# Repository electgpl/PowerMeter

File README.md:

# Power Meter v1 

Este es un medidor de potencia continua y alterna diseñado en base al microcontrolador AVR linea MEGA compatible ArduinoIDE.

  - Core AVR - **ARDUINO PRO MINI 5V**
  - Bootloader UART Arduino Compatible
  - ISP Compatible
  - Serial Terminal/Debug
  - Puerto para LCD I2C
  - Medidor de corriente ACS712 (Compatible 5, 20 y 30A) 
  - Medidor de Tensión **Directo** con atenuación resistiva y montado sobre 2.5V (Cero)
  - Fuente de alimentación integrada

## Lenguajes Compatibles

  - C
  - C++
  - Basic
  - Ensamblador
  - Ladder
  - y mas...
  
## Diseño y Desarrollo

> Diseñado en dos capas con SMD y THT
> Los componentes SMD son extraídos directamente de una placa Arduino Pro Mini 5V y Modulo ACS712
> Los componentes THT se adquieren con facilidad en los comercios.
>                           
> PCB creado en [JLCPCB].
> Diseño realizado en [Eagle].

### Instalación

Todos los archivos se encuentran disponibles en este repositorio, diagramas, pcb, etc...

### Pendientes

 - Código para el medidor de continua para la incorporación en fuentes de alimentación.
 - Mejoras en la aislación de seguridad eléctrica

License
----

MIT

**Free Software, Hell Yeah!**

[JLCPCB]: <https://jlcpcb.com/>
[Eagle]: <https://www.autodesk.com/products/eagle/overview>

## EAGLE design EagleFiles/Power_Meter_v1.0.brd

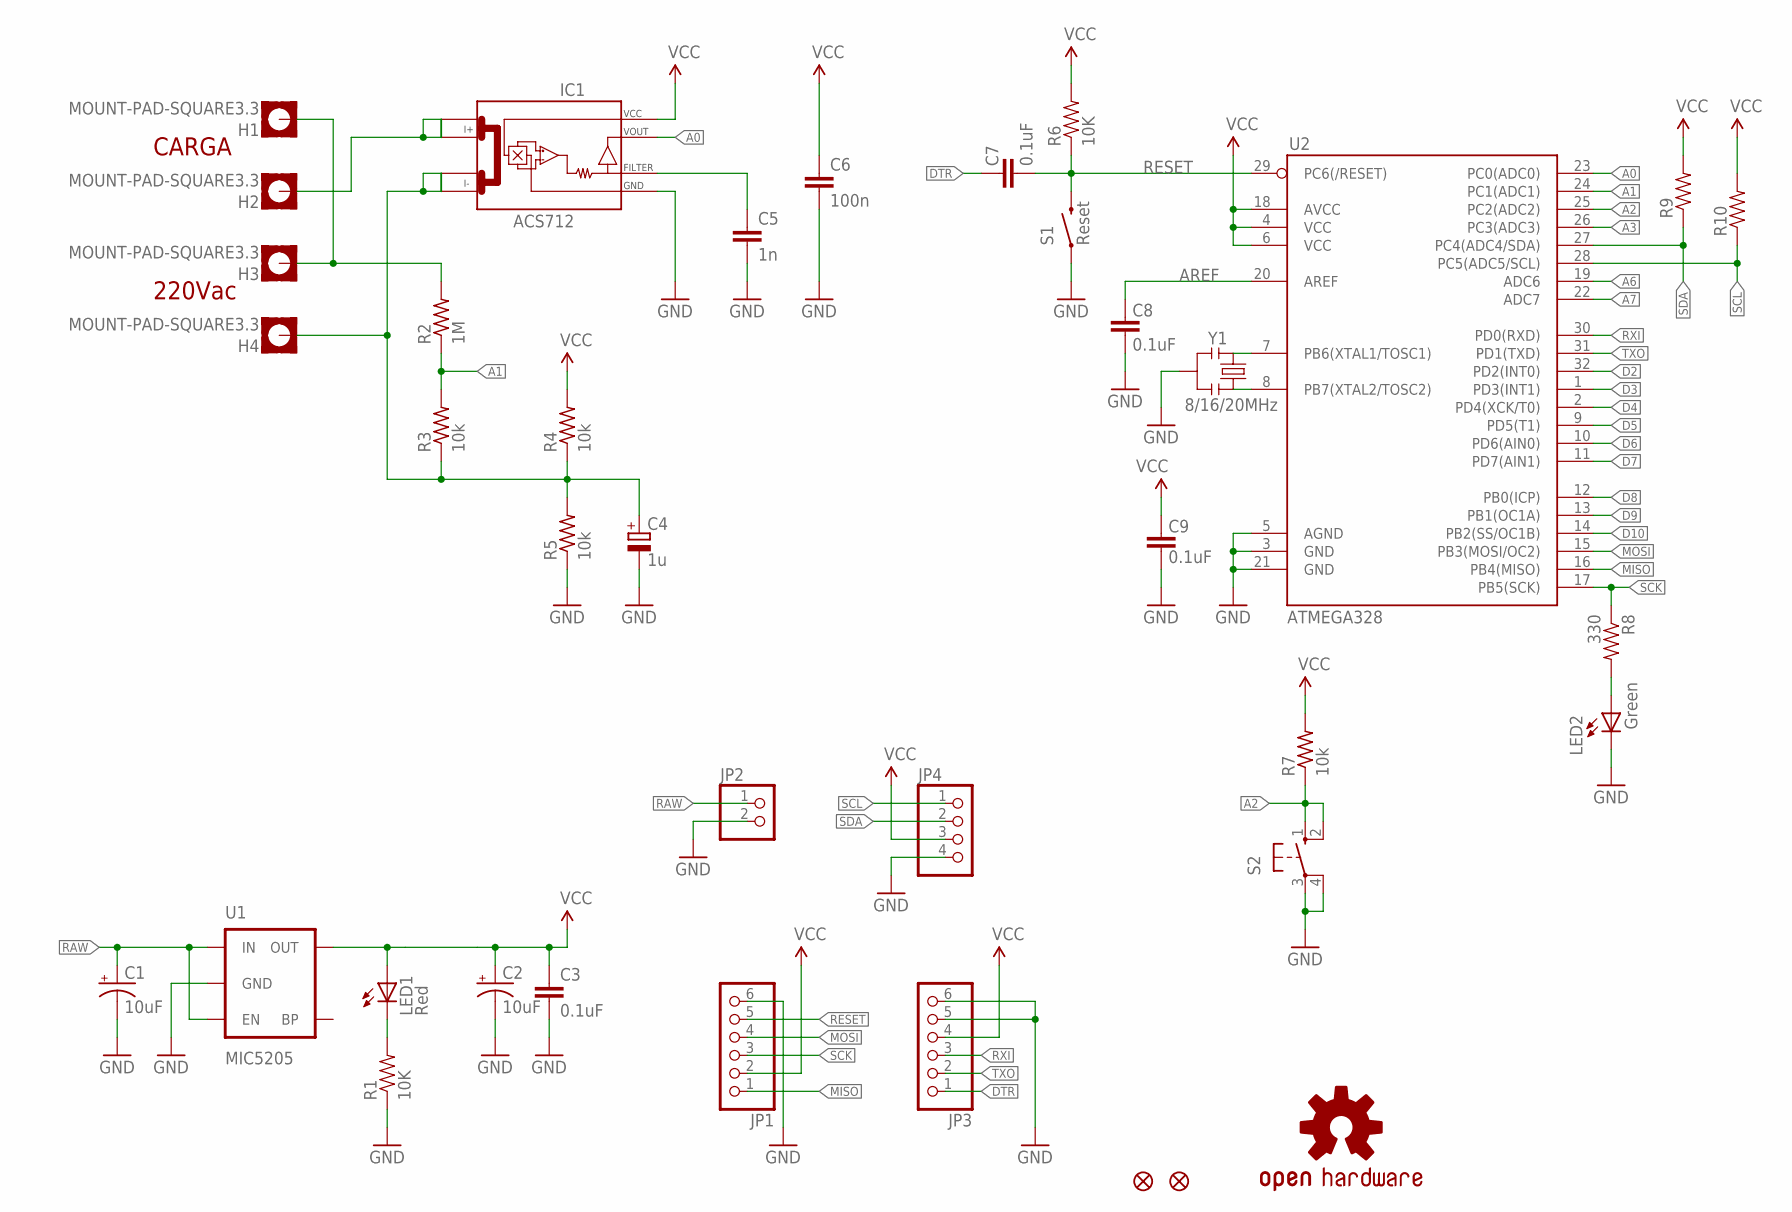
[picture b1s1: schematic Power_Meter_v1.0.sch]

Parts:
C1, C2: 10uF; EIA3216
C3, C7, C8, C9: 0.1uF; 0603-CAP
C4: 1u; E2-5
C5: 1n; C0805K
C6: 100n; C0805K
H1, H2, H3, H4: MOUNT-PAD-SQUARE3.3; 3,3-PAD-SQUARE
IC1: ACS712; SO08
JP1, JP3: PINHD-1X6; 1X06
JP2: PINHD-1X2; 1X02
JP4: PINHD-1X4; 1X04
JP5, JP6: FIDUCIAL1X2.5; FIDUCIAL-1X2.5
LED1: Red; 0603-LED-ALT1
LED2: Green; 0603-LED-ALT1
R1, R6: 10K; 0603-RES
R2: 1M; 0204/7
R3, R4, R5, R7: 10k; 0204/7
R8: 330; 0603-RES
R9, R10: RESISTOR0603-RES; 0603-RES
S1: Reset; TACTILE-SWITCH-SMD-ALT01
S2: 10-XX; B3F-10XX
U1: MIC5205; SOT23-5
U2: ATMEGA328; TQFP32-08
U$5: OSHW-LOGOS; OSHW-LOGO-S
Y1: 8/16/20MHz; RESONATOR-SMD-1:1

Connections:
A0: IC1.7 (VOUT), U2.23 (PC0(ADC0))
A1: R2.1, R3.2, U2.24 (PC1(ADC1))
A2: R7.1, S2.1 (S), S2.2 (S1), U2.25 (PC2(ADC2))
A3: U2.26 (PC3(ADC3))
A6: U2.19 (ADC6)
A7: U2.22 (ADC7)
AREF: C8.2, U2.20 (AREF)
D2: U2.32 (PD2(INT0))
D3: U2.1 (PD3(INT1))
D4: U2.2 (PD4(XCK/T0))
D5: U2.9 (PD5(T1))
D6: U2.10 (PD6(AIN0))
D7: U2.11 (PD7(AIN1))
D8: U2.12 (PB0(ICP))
D9: U2.13 (PB1(OC1A))
D10: U2.14 (PB2(SS/OC1B))
DTR: C7.2, JP3.1
GND: C1.C (-), C2.C (-), C3.2, C4.-, C5.2, C6.2, C8.1, C9.1, IC1.5 (GND), JP1.6, JP2.2, JP3.5, JP3.6, JP4.4, LED2.C, R1.1, R5.1, S1.1, S1.2 (1), S2.3, S2.4 (P1), U1.2 (GND), U2.3 (GND), U2.5 (AGND), U2.21 (GND), Y1.2
MISO: JP1.1, U2.16 (PB4(MISO))
MOSI: JP1.4, U2.15 (PB3(MOSI/OC2))
unnamed: LED2.A, R8.2
unnamed: U2.8 (PB7(XTAL2/TOSC2)), Y1.3
unnamed: U2.7 (PB6(XTAL1/TOSC1)), Y1.1
unnamed: H1.B3,3, H3.B3,3, R2.2
unnamed: C5.1, IC1.6 (FILTER)
unnamed: H2.B3,3, IC1.1 (I+_0), IC1.2 (I+_1)
unnamed: LED1.C, R1.2
unnamed: C4.+, H4.B3,3, IC1.3 (I-_0), IC1.4 (I-_1), R3.1, R4.1, R5.2
RAW: C1.A (+), JP2.1, U1.1 (IN), U1.3 (EN)
RESET: C7.1, JP1.5, R6.1, S1.3 (2), S1.4 (2), U2.29 (PC6(/RESET))
RXI: JP3.3, U2.30 (PD0(RXD))
SCK: JP1.3, R8.1, U2.17 (PB5(SCK))
SCL: JP4.1, R10.1, U2.28 (PC5(ADC5/SCL))
SDA: JP4.2, R9.1, U2.27 (PC4(ADC4/SDA))
TXO: JP3.2, U2.31 (PD1(TXD))
VCC: C2.A (+), C3.1, C6.1, C9.2, IC1.8 (VCC), JP1.2, JP3.4, JP4.3, LED1.A, R4.2, R6.2, R7.2, R9.2, R10.2, U1.5 (OUT), U2.4 (VCC), U2.6 (VCC), U2.18 (AVCC)

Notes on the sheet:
CARGA
220Vac

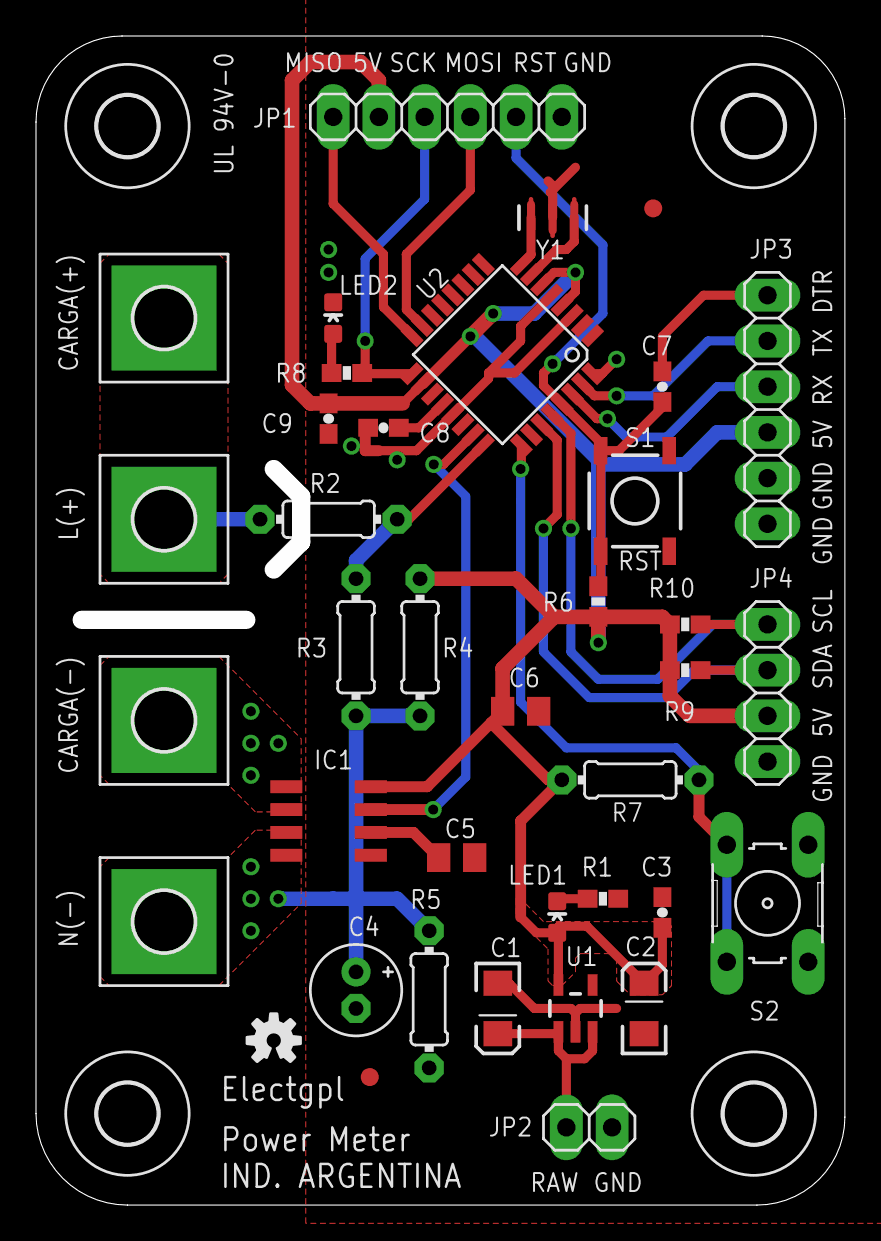
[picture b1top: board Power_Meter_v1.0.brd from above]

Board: 2 copper layers, 43.9 x 63.9 mm, 42 parts (0 on the bottom side), 24 nets.

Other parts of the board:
U$1, U$2, U$3, U$4: 3,3

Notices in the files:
parts and their libraries:
SparkFun-Aesthetics: Licensing: CC v3.0 Share-Alike You are welcome to use this library for commercial purposes.
